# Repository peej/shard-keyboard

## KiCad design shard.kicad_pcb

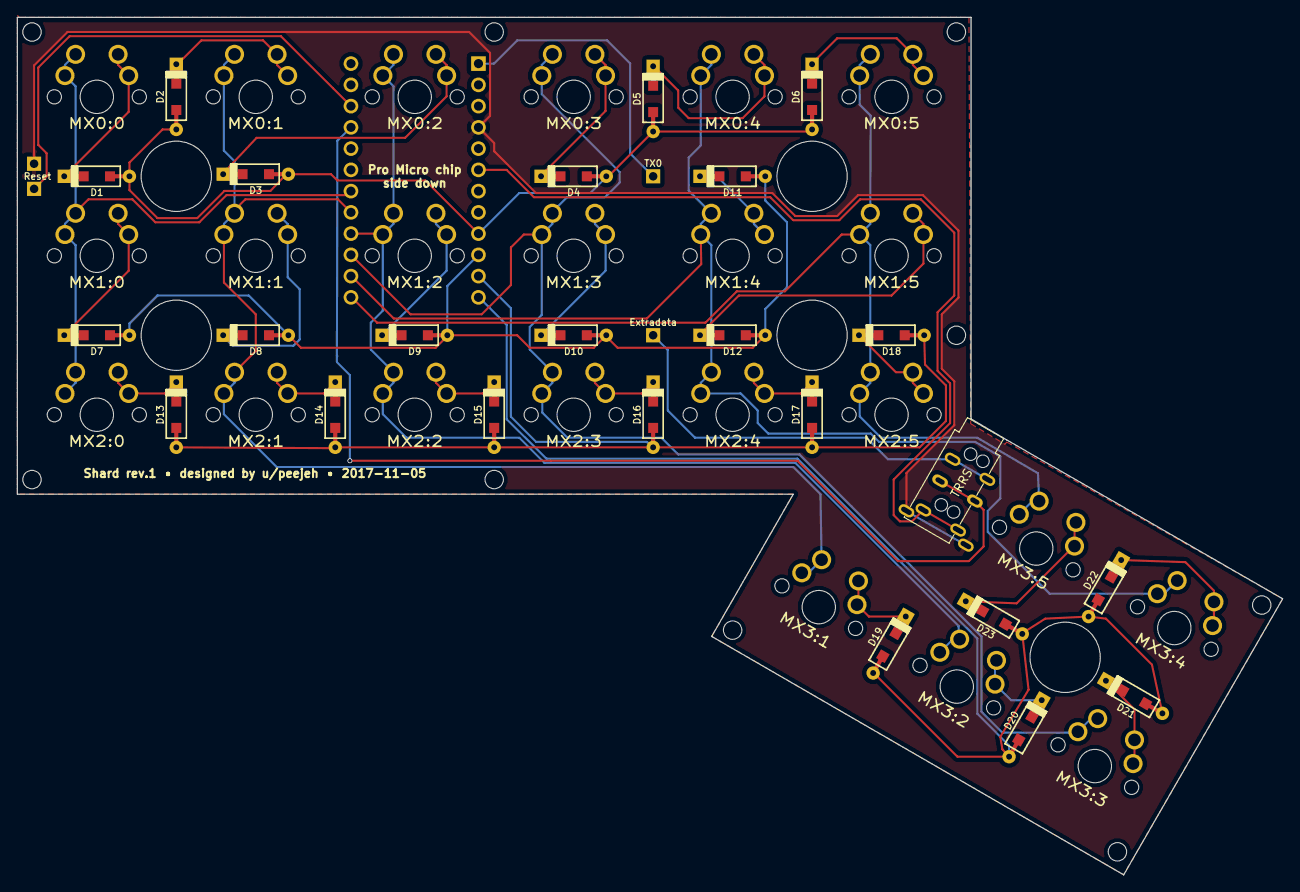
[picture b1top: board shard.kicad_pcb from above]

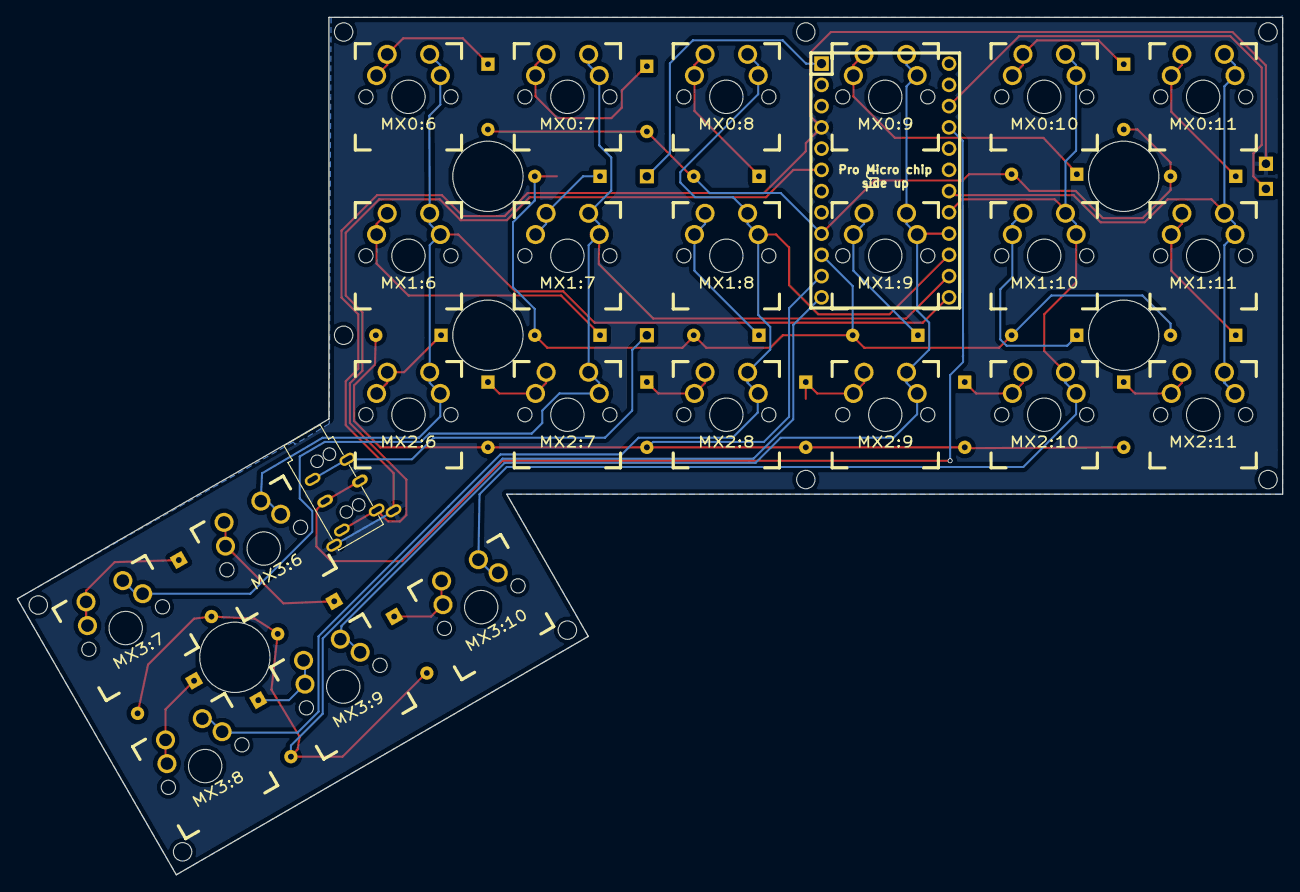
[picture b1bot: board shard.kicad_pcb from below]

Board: 2 copper layers, 151.2 x 102.5 mm, 66 parts (24 on the bottom side), 39 nets.

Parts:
D1, D2, D3, D4, D5, D6, D7, D8, D9, D10, D11, D12, D13, D14, D15, D16, D17, D18, D19, D20, D21, D22, D23: DIODE; D_SOD123_axial
EXTRADATA1: Extradata; PIN_1_SQUARE
GROUND1: Ground; PIN_1_SQUARE
J1: TRRS; PJ320A_3.5mm_Jack
M2, M2#2, M2#3, M2#4, M2#5, M2#6, M2#7, M2#8, M2#9: MountingHole_2.2mm_M2
M8, M8#2, M8#3, M8#4, M8#5: MountingHole_8.4mm_M8
MX0:0: MX0:11; MX_DoubleSided
MX0:1: MX0:10; MX_DoubleSided
MX0:2: MX0:9; MX_DoubleSided
MX0:3: MX0:8; MX_DoubleSided
MX0:4: MX0:7; MX_DoubleSided
MX0:5: MX0:6; MX_DoubleSided
MX1:0: MX1:11; MX_DoubleSided
MX1:1: MX1:10; MX_DoubleSided
MX1:2: MX1:9; MX_DoubleSided
MX1:3: MX1:8; MX_DoubleSided
MX1:4: MX1:7; MX_DoubleSided
MX1:5: MX1:6; MX_DoubleSided
MX2:0: MX2:11; MX_DoubleSided
MX2:1: MX2:10; MX_DoubleSided
MX2:2: MX2:9; MX_DoubleSided
MX2:3: MX2:8; MX_DoubleSided
MX2:4: MX2:7; MX_DoubleSided
MX2:5: MX2:6; MX_DoubleSided
MX3:1: MX3:10; MX_DoubleSided
MX3:2: MX3:9; MX_DoubleSided
MX3:3: MX3:8; MX_DoubleSided
MX3:4: MX3:7; MX_DoubleSided
MX3:5: MX3:6; MX_DoubleSided
RESET1: Reset; PIN_1_SQUARE
TX0: TX0; PIN_1_SQUARE
U1: ARDUINO_PRO_MICRO

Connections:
/Col0: MX0:0.1, MX1:0.1, MX2:0.1, U1.18
/Col1: MX0:1.1, MX1:1.1, MX2:1.1, MX3:1.1, U1.17
/Col2: MX0:2.1, MX1:2.1, MX2:2.1, MX3:2.1, U1.16
/Col3: MX0:3.1, MX1:3.1, MX2:3.1, MX3:3.1, U1.15
/Col4: MX0:4.1, MX1:4.1, MX2:4.1, MX3:4.1, U1.14
/Col5: MX0:5.1, MX1:5.1, MX2:5.1, MX3:5.1, U1.13
/Row0: D1.2, D2.2, D3.2, D4.2, D5.2, D6.2, U1.9
/Row1: D7.2, D8.2, D9.2, D10.2, D11.2, D12.2, U1.10
/Row2: D13.2, D14.2, D15.2, D16.2, D17.2, D18.2, U1.11
/Row3: D19.2, D20.2, D21.2, D22.2, D23.2, U1.12
GND: GROUND1.1, J1.4, U1.4
unnamed: D1.1, MX0:0.2
unnamed: D2.1, MX0:1.2
unnamed: D3.1, MX0:2.2
unnamed: D4.1, MX0:3.2
unnamed: D5.1, MX0:4.2
unnamed: D6.1, MX0:5.2
unnamed: D7.1, MX1:0.2
unnamed: D8.1, MX1:1.2
unnamed: D9.1, MX1:2.2
unnamed: D10.1, MX1:3.2
unnamed: D11.1, MX1:4.2
unnamed: D12.1, MX1:5.2
unnamed: D13.1, MX2:0.2
unnamed: D14.1, MX2:1.2
unnamed: D15.1, MX2:2.2
unnamed: D16.1, MX2:3.2
unnamed: D17.1, MX2:4.2
unnamed: D18.1, MX2:5.2
unnamed: D19.1, MX3:1.2
unnamed: D20.1, MX3:2.2
unnamed: D21.1, MX3:3.2
unnamed: D22.1, MX3:4.2
unnamed: D23.1, MX3:5.2
unnamed: EXTRADATA1.1, J1.3
unnamed: J1.1, U1.6
unnamed: RESET1.1, U1.22
unnamed: TX0.1, U1.1
VCC: J1.2, U1.21

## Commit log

2017-11-11 Initial add of Kicad files
2017-11-12 Add plate PCB design
2017-11-12 Add holes for standoffs and re-route
2017-11-13 Move M2 mounting holes in from board edge
2017-11-13 Re-align diodes
2017-11-14 Move TRRS away from switches to improve clearance
2017-11-18 Adjust Pro Micro pinout to match Let's Split
2017-11-21 Add case base to plate PCB
